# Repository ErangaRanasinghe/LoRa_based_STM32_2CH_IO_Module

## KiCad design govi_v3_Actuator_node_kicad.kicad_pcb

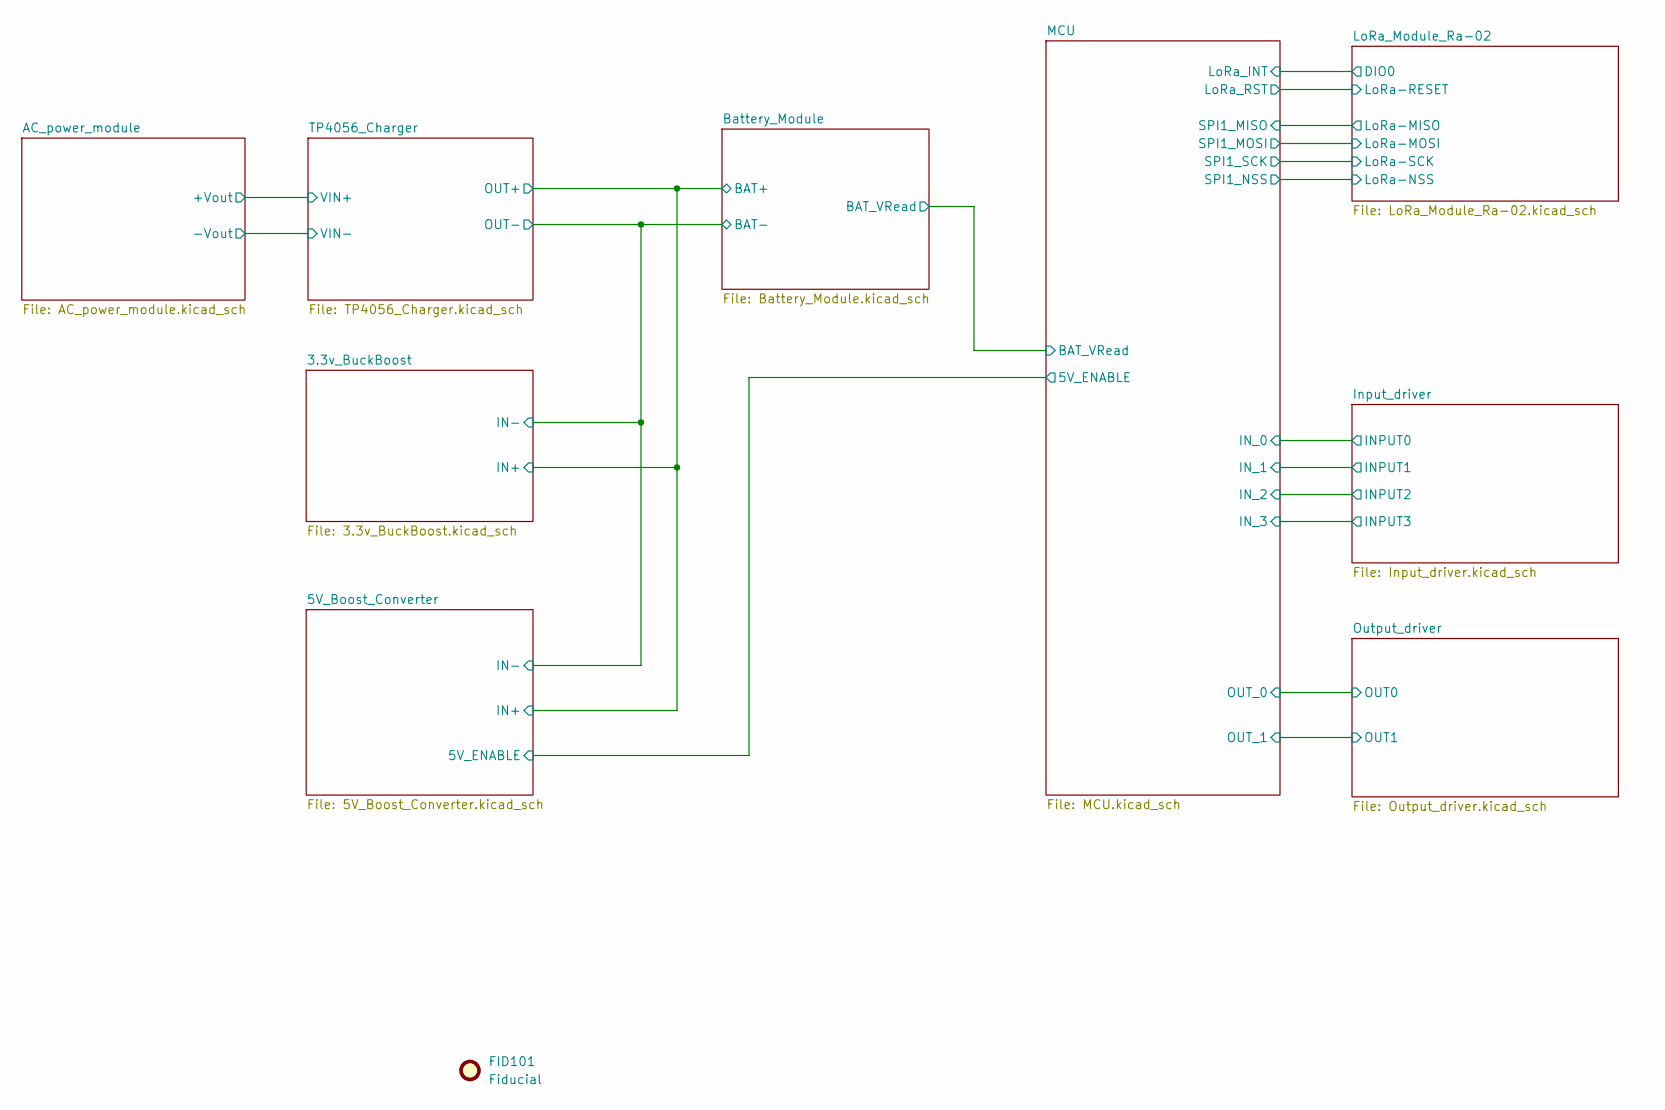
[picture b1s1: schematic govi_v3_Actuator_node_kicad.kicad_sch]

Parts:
FID101: Fiducial; Fiducial_1mm_Mask3mm

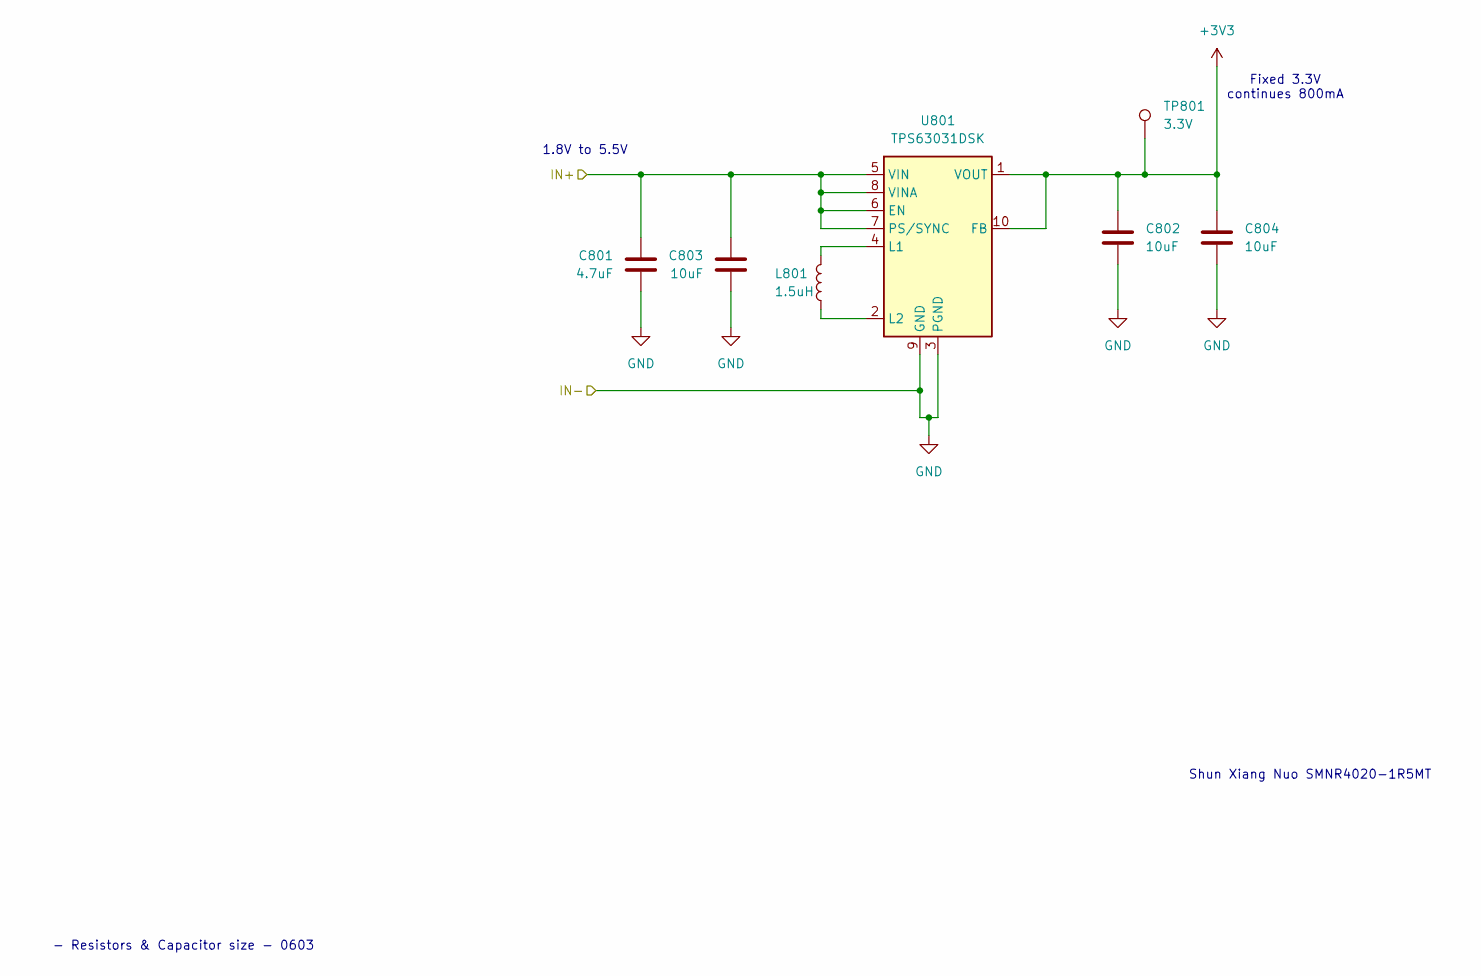
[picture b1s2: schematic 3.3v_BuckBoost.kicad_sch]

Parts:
C801: 4.7uF; C_0603_1608Metric_Pad1.08x0.95mm_HandSolder
C802, C803, C804: 10uF; C_0603_1608Metric_Pad1.08x0.95mm_HandSolder
L801: 1.5uH; L_KOHERelec_MDA7030
TP801: 3.3V; TestPoint_Pad_D1.0mm
U801: TPS63031DSK; WSON-10-1EP_2.5x2.5mm_P0.5mm_EP1.2x2mm

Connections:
+3V3: C802.1, C804.1, TP801.1, U801.1 (VOUT), U801.10 (FB); also elsewhere on the board
/Battery_Module/BAT(+): C801.1, C803.1, U801.5 (VIN), U801.6 (EN), U801.7 (PS/SYNC), U801.8 (VINA); also elsewhere on the board
GND: C801.2, C802.2, C803.2, C804.2, U801.3 (PGND), U801.9 (GND), U801.11 (PGND); also elsewhere on the board
unnamed: L801.1, U801.4 (L1)
unnamed: L801.2, U801.2 (L2)

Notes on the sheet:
Shun Xiang Nuo SMNR4020-1R5MT
- Resistors & Capacitor size - 0603
1.8V to 5.5V
Fixed 3.3V continues 800mA

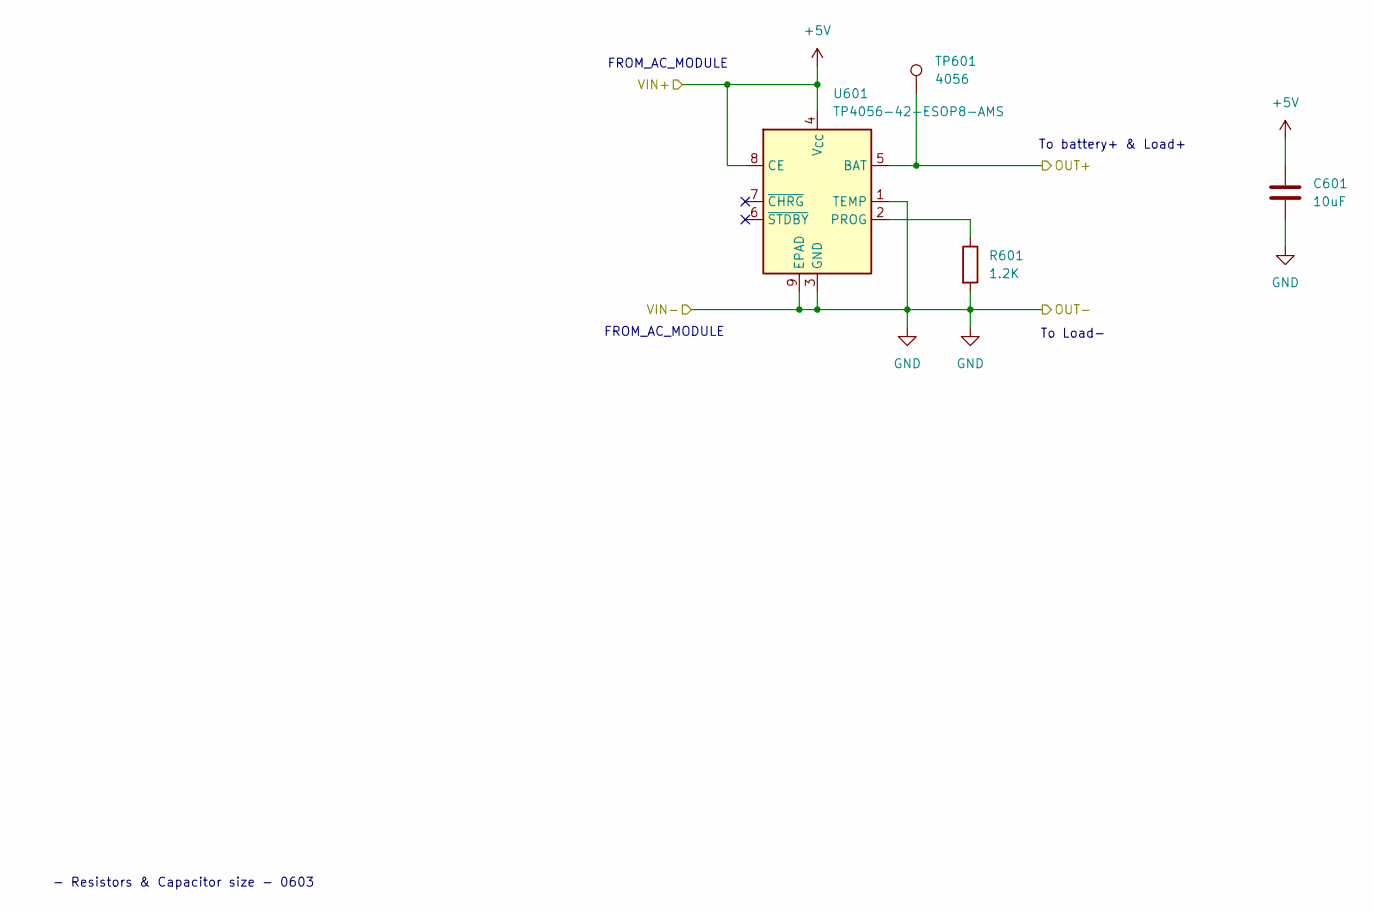
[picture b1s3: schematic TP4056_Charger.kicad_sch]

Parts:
C601: 10uF; C_0603_1608Metric_Pad1.08x0.95mm_HandSolder
R601: 1.2K; R_0603_1608Metric_Pad0.98x0.95mm_HandSolder
TP601: 4056; TestPoint_Pad_D1.0mm
U601: TP4056-42-ESOP8-AMS; SOIC-8-1EP_3.9x4.9mm_P1.27mm_EP2.41x3.3mm_ThermalVias

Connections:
+5V: C601.1, U601.4 (V_{CC}), U601.8 (CE); also elsewhere on the board
/Battery_Module/BAT(+): TP601.1, U601.5 (BAT); also elsewhere on the board
GND: C601.2, R601.2, U601.1 (TEMP), U601.3 (GND), U601.9 (EPAD); also elsewhere on the board
unnamed: R601.1, U601.2 (PROG)

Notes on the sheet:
- Resistors & Capacitor size - 0603
To battery+ & Load+
To Load-
FROM_AC_MODULE

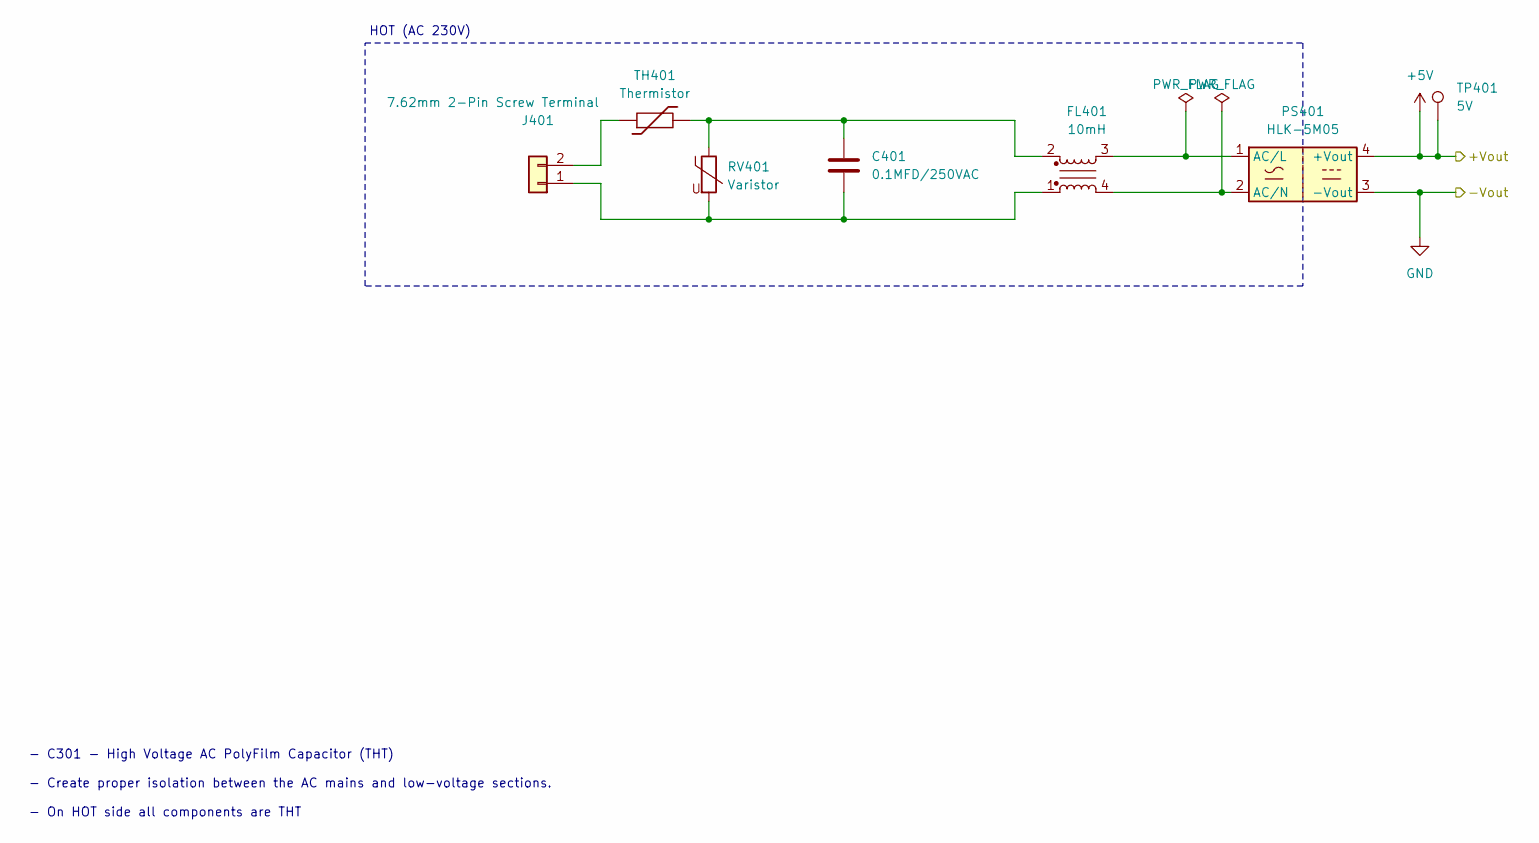
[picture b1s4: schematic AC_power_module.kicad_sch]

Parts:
C401: 0.1MFD/250VAC; C_Rect_L11.5mm_W5.0mm_P10.00mm_MKT
FL401: 10mH; B82730U3451A020-ferrite-core-inductor
J401: 7.62mm 2-Pin Screw Terminal; PhoenixContact_MCV_1,5_2-G-5.08_1x02_P5.08mm_Vertical
PS401: HLK-5M05; HLK5M05
RV401: Varistor; RV_Disc_D12mm_W5.1mm_P7.5mm
TH401: Thermistor; B57236S0250M000-Thermister
TP401: 5V; TestPoint_Pad_D1.0mm

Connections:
+5V: PS401.4 (+Vout), TP401.1; also elsewhere on the board
GND: PS401.3 (-Vout); also elsewhere on the board
unnamed: C401.1, FL401.2, RV401.1, TH401.2
unnamed: C401.2, FL401.1, J401.1, RV401.2
unnamed: J401.2, TH401.1
unnamed: FL401.3, PS401.1 (AC/L)
unnamed: FL401.4, PS401.2 (AC/N)

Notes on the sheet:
HOT (AC 230V)
- C301 - High Voltage AC PolyFilm Capacitor (THT) - Create proper isolation between the AC mains and low-voltage sections. - On HOT side all components are THT

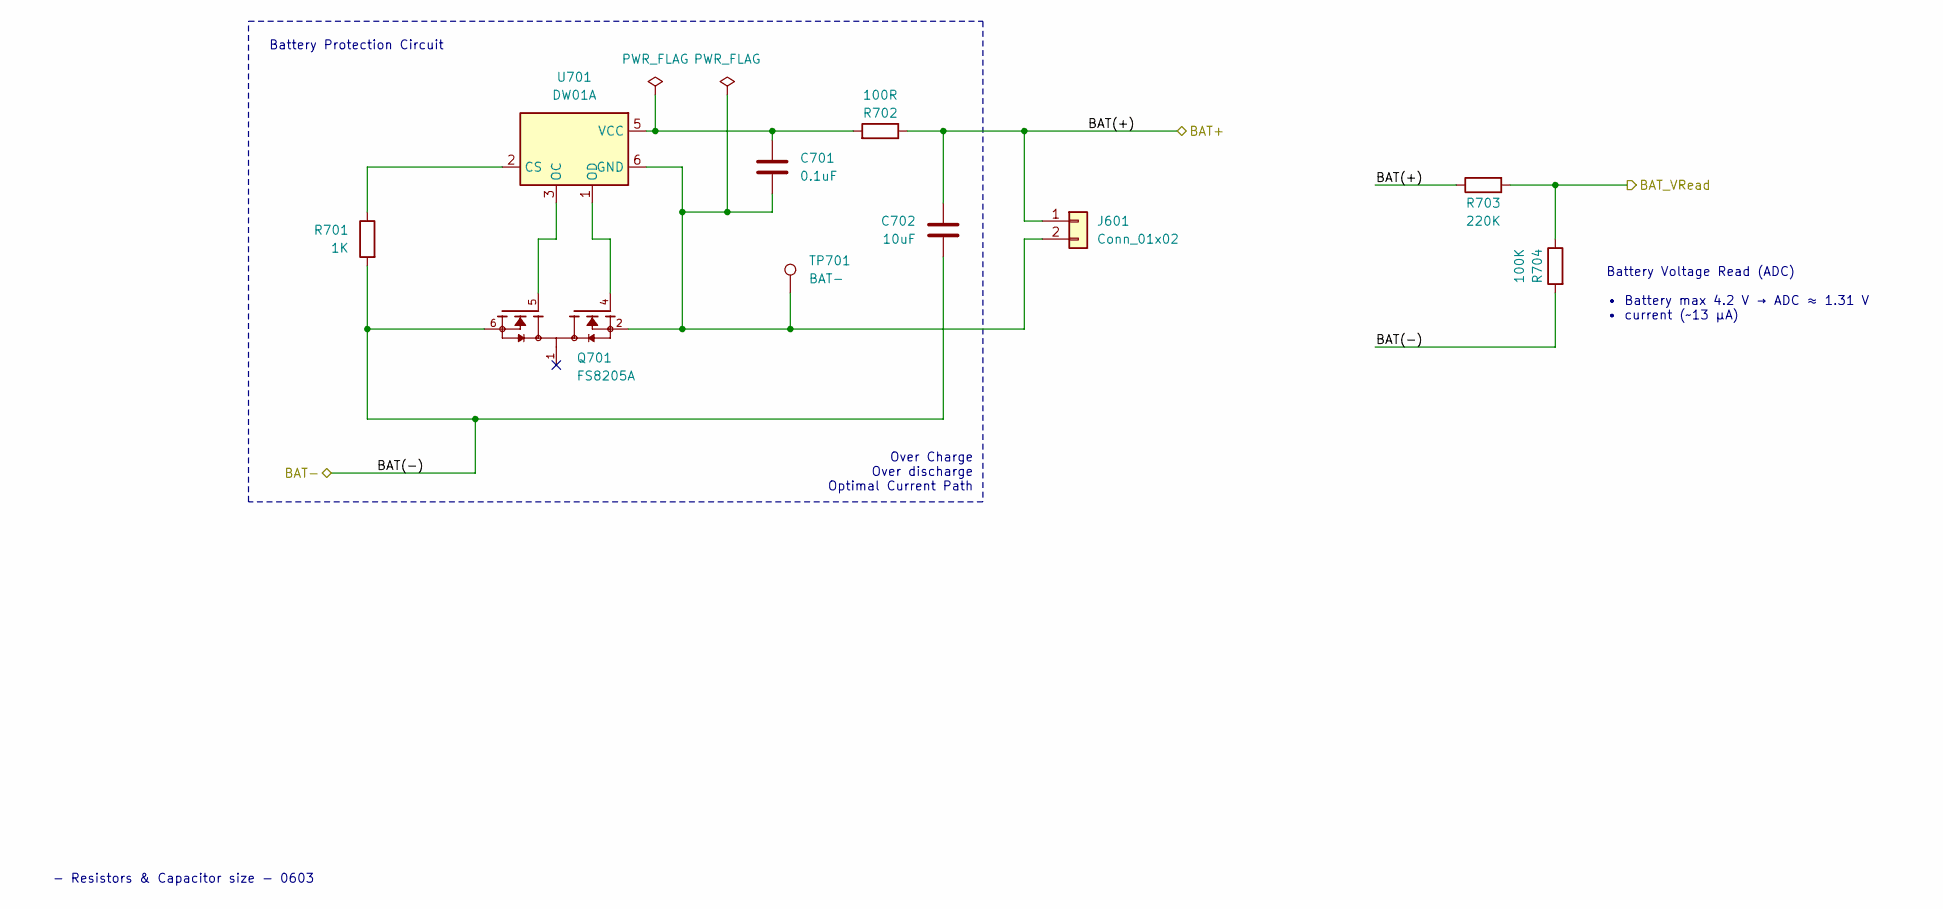
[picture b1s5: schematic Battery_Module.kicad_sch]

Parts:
C701: 0.1uF; C_0603_1608Metric_Pad1.08x0.95mm_HandSolder
C702: 10uF; C_0603_1608Metric_Pad1.08x0.95mm_HandSolder
J601: Conn_01x02; PhoenixContact_MCV_1,5_2-G-5.08_1x02_P5.08mm_Vertical
Q701: FS8205A; SOP65P640X120-8N; PARTREV 1.7
R701: 1K; R_0603_1608Metric_Pad0.98x0.95mm_HandSolder
R702: 100R; R_0603_1608Metric_Pad0.98x0.95mm_HandSolder
R703: 220K; R_0603_1608Metric_Pad0.98x0.95mm_HandSolder
R704: 100K; R_0603_1608Metric_Pad0.98x0.95mm_HandSolder
TP701: BAT-; TestPoint_Pad_D1.0mm
U701: DW01A; SOT-23-6

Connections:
/Battery_Module/BAT(+): C702.1, J601.1, R702.1, R703.1; also elsewhere on the board
/Battery_Module/BAT_VRead: R703.2, R704.1; also elsewhere on the board
GND: C702.2, Q701.6, Q701.7, R701.2, R704.2; also elsewhere on the board
unnamed: C701.2, J601.2, Q701.2, Q701.3, TP701.1, U701.6 (GND)
unnamed: R701.1, U701.2 (CS)
unnamed: Q701.5, U701.3 (OC)
unnamed: Q701.4, U701.1 (OD)
unnamed: C701.1, R702.2, U701.5 (VCC)

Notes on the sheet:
Over Charge Over discharge Optimal Current Path
- Resistors & Capacitor size - 0603
Battery Protection Circuit
Battery Voltage Read (ADC) • Battery max 4.2 V → ADC ≈ 1.31 V • current (~13 µA)

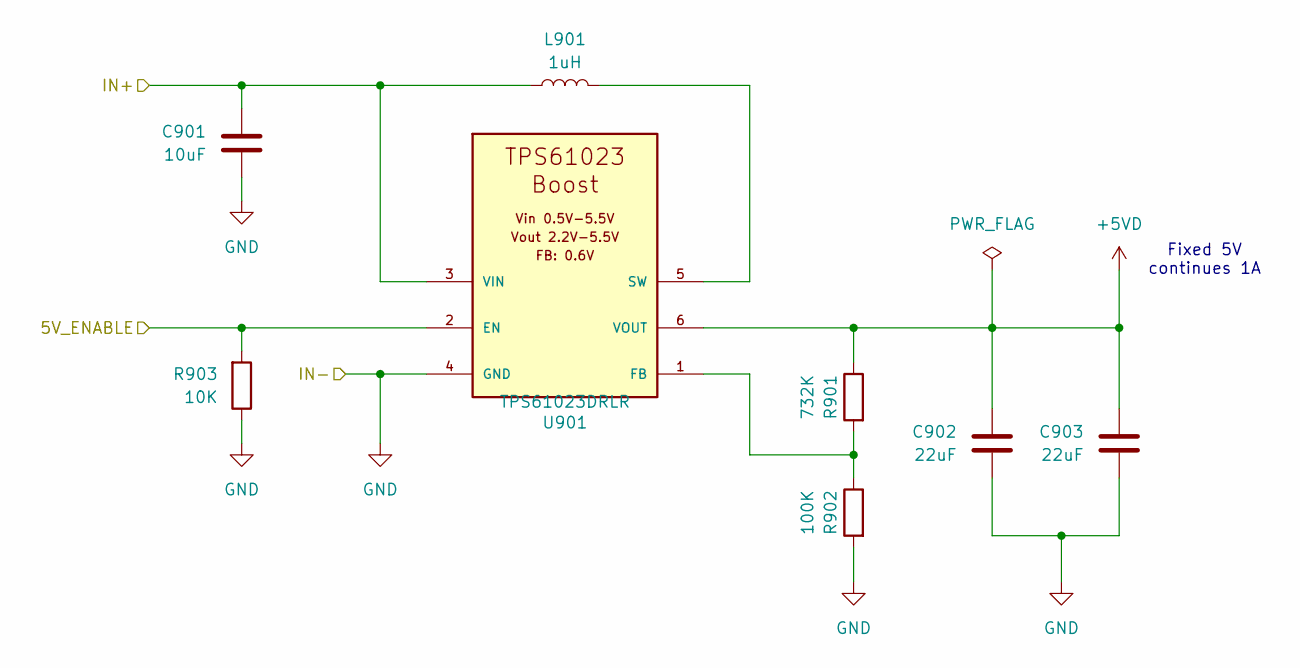
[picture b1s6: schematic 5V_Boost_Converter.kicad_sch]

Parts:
C901: 10uF; C_0603_1608Metric_Pad1.08x0.95mm_HandSolder
C902, C903: 22uF; C_0603_1608Metric_Pad1.08x0.95mm_HandSolder
L901: 1uH; L_Cenker_CKCS4030
R901: 732K; R_0603_1608Metric_Pad0.98x0.95mm_HandSolder
R902: 100K; R_0603_1608Metric_Pad0.98x0.95mm_HandSolder
R903: 10K; R_0402_1005Metric_Pad0.72x0.64mm_HandSolder
U901: TPS61023DRLR; SOT563-ORI

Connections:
+5VD: C902.1, C903.1, R901.1, U901.6 (VOUT); also elsewhere on the board
/5V_Boost_Converter/5V_ENABLE: R903.2, U901.2 (EN); also elsewhere on the board
/Battery_Module/BAT(+): C901.1, L901.1, U901.3 (VIN); also elsewhere on the board
GND: C901.2, C902.2, C903.2, R902.2, R903.1, U901.4 (GND); also elsewhere on the board
unnamed: R901.2, R902.1, U901.1 (FB)
unnamed: L901.2, U901.5 (SW)

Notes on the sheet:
Fixed 5V continues 1A

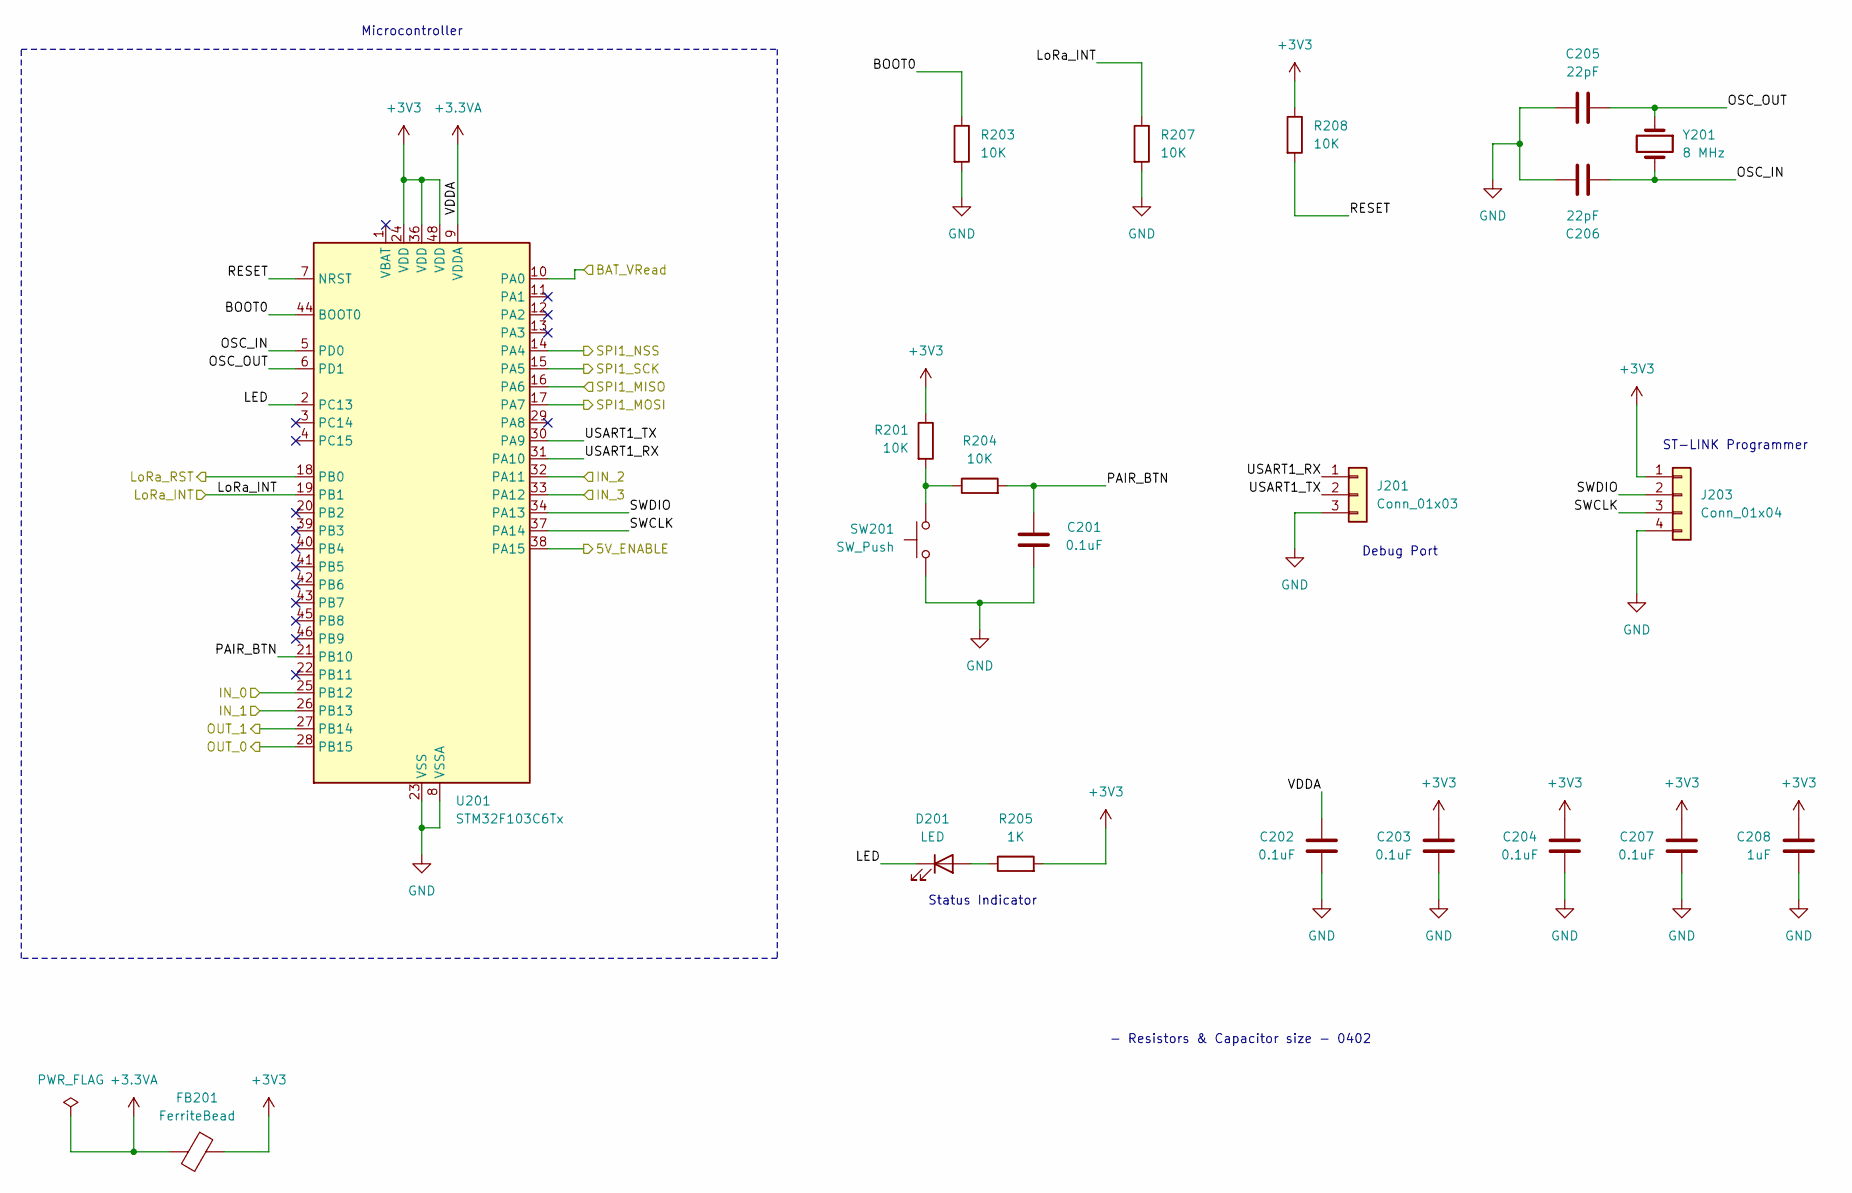
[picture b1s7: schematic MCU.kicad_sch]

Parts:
C201, C202, C203, C204, C207: 0.1uF; C_0402_1005Metric_Pad0.74x0.62mm_HandSolder
C205, C206: 22pF; C_0402_1005Metric_Pad0.74x0.62mm_HandSolder
C208: 1uF; C_0402_1005Metric_Pad0.74x0.62mm_HandSolder
D201: LED; LED_D3.0mm
FB201: FerriteBead; R_0402_1005Metric_Pad0.72x0.64mm_HandSolder
J201: Conn_01x03; PinHeader_1x03_P2.54mm_Vertical
J203: Conn_01x04; PinHeader_1x04_P2.54mm_Vertical
R201, R203, R204, R207, R208: 10K; R_0402_1005Metric_Pad0.72x0.64mm_HandSolder
R205: 1K; R_0402_1005Metric_Pad0.72x0.64mm_HandSolder
SW201: SW_Push; PinHeader_1x02_P2.54mm_Vertical
U201: STM32F103C6Tx; LQFP-48_7x7mm_P0.5mm
Y201: 8 MHz; Crystal_HC49-4H_Vertical

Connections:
+3.3VA: C202.1, FB201.2, U201.9 (VDDA)
+3V3: C203.1, C204.1, C207.1, C208.1, FB201.1, J203.1, R201.1, R205.2, R208.1, U201.24 (VDD), U201.36 (VDD), U201.48 (VDD); also elsewhere on the board
/5V_Boost_Converter/5V_ENABLE: U201.38 (PA15); also elsewhere on the board
/Battery_Module/BAT_VRead: U201.10 (PA0); also elsewhere on the board
/Input_driver/INPUT0: U201.25 (PB12); also elsewhere on the board
/Input_driver/INPUT1: U201.26 (PB13); also elsewhere on the board
/Input_driver/INPUT2: U201.32 (PA11); also elsewhere on the board
/Input_driver/INPUT3: U201.33 (PA12); also elsewhere on the board
/LoRa_Module_Ra-02/LoRa-MISO: U201.16 (PA6); also elsewhere on the board
/LoRa_Module_Ra-02/LoRa-MOSI: U201.17 (PA7); also elsewhere on the board
/LoRa_Module_Ra-02/LoRa-NSS: U201.14 (PA4); also elsewhere on the board
/LoRa_Module_Ra-02/LoRa-RESET: U201.18 (PB0); also elsewhere on the board
/LoRa_Module_Ra-02/LoRa-SCK: U201.15 (PA5); also elsewhere on the board
/MCU/BOOT0: R203.1, U201.44 (BOOT0)
/MCU/LED: D201.1 (K), U201.2 (PC13)
/MCU/LoRa_INT: R207.1, U201.19 (PB1); also elsewhere on the board
/MCU/OSC_IN: C206.1, U201.5 (PD0), Y201.2
/MCU/OSC_OUT: C205.1, U201.6 (PD1), Y201.1
/MCU/OUT_0: U201.28 (PB15); also elsewhere on the board
/MCU/OUT_1: U201.27 (PB14); also elsewhere on the board
/MCU/PAIR_BTN: C201.1, R204.2, U201.21 (PB10)
/MCU/RESET: R208.2, U201.7 (NRST)
/MCU/SWCLK: J203.3, U201.37 (PA14)
/MCU/SWDIO: J203.2, U201.34 (PA13)
/MCU/USART1_RX: J201.1, U201.31 (PA10)
/MCU/USART1_TX: J201.2, U201.30 (PA9)
GND: C201.2, C202.2, C203.2, C204.2, C205.2, C206.2, C207.2, C208.2, J201.3, J203.4, R203.2, R207.2, SW201.1, U201.8 (VSSA), U201.23 (VSS), U201.35 (VSS), U201.47 (VSS); also elsewhere on the board
unnamed: D201.2 (A), R205.1
unnamed: R201.2, R204.1, SW201.2

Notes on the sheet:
Status Indicator
Debug Port
- Resistors & Capacitor size - 0402
ST-LINK Programmer
Microcontroller

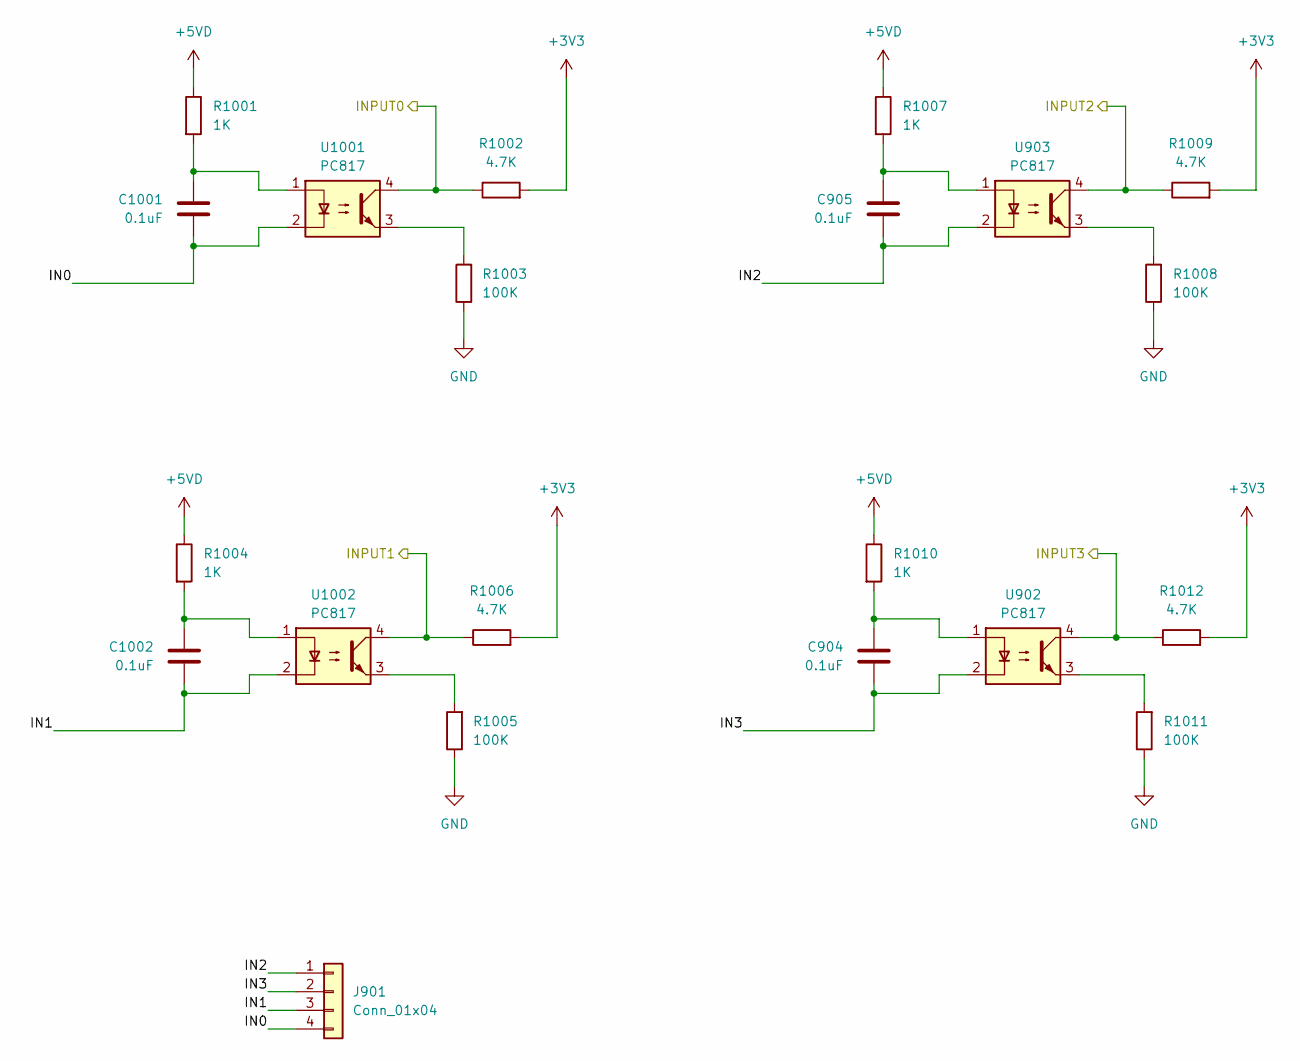
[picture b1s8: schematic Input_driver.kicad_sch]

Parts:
C904, C905, C1001, C1002: 0.1uF; C_0402_1005Metric_Pad0.74x0.62mm_HandSolder
J901: Conn_01x04; PhoenixContact_MCV_1,5_4-G-5.08_1x04_P5.08mm_Vertical
R1001, R1004, R1007, R1010: 1K; R_0603_1608Metric_Pad0.98x0.95mm_HandSolder
R1002, R1006, R1009, R1012: 4.7K; R_0402_1005Metric_Pad0.72x0.64mm_HandSolder
R1003, R1005, R1008, R1011: 100K; R_0402_1005Metric_Pad0.72x0.64mm_HandSolder
U902, U903, U1001, U1002: PC817; DIP-4_W7.62mm

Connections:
+3V3: R1002.2, R1006.2, R1009.2, R1012.2; also elsewhere on the board
+5VD: R1001.1, R1004.1, R1007.1, R1010.1; also elsewhere on the board
/Input_driver/IN0: C1001.2, J901.4, U1001.2
/Input_driver/IN1: C1002.2, J901.3, U1002.2
/Input_driver/IN2: C905.2, J901.1, U903.2
/Input_driver/IN3: C904.2, J901.2, U902.2
/Input_driver/INPUT0: R1002.1, U1001.4; also elsewhere on the board
/Input_driver/INPUT1: R1006.1, U1002.4; also elsewhere on the board
/Input_driver/INPUT2: R1009.1, U903.4; also elsewhere on the board
/Input_driver/INPUT3: R1012.1, U902.4; also elsewhere on the board
GND: R1003.1, R1005.1, R1008.1, R1011.1; also elsewhere on the board
unnamed: C904.1, R1010.2, U902.1
unnamed: C905.1, R1007.2, U903.1
unnamed: C1001.1, R1001.2, U1001.1
unnamed: C1002.1, R1004.2, U1002.1
unnamed: R1003.2, U1001.3
unnamed: R1005.2, U1002.3
unnamed: R1008.2, U903.3
unnamed: R1011.2, U902.3

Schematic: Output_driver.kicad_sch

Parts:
C1101, C1102: 0.1uF; C_0402_1005Metric_Pad0.74x0.62mm_HandSolder
J1001: Conn_01x04; PhoenixContact_MCV_1,5_4-G-5.08_1x04_P5.08mm_Vertical
Q1002, Q1101: BC817-40; SOT-23
R1101, R1104: 10R 0805; R_0805_2012Metric_Pad1.20x1.40mm_HandSolder
R1102, R1103: 1K; R_0603_1608Metric_Pad0.98x0.95mm_HandSolder
U1101, U1102: G3MB-202P; G3MB202PLDC5

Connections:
+5VD: R1101.1, R1104.1; also elsewhere on the board
/MCU/OUT_0: R1102.1; also elsewhere on the board
/MCU/OUT_1: R1103.1; also elsewhere on the board
/Output_driver/OUT0_11: J1001.2, U1101.11
/Output_driver/OUT0_14: J1001.1, U1101.14
/Output_driver/OUT1_11: J1001.4, U1102.11
/Output_driver/OUT1_14: J1001.3, U1102.14
GND: Q1002.2 (E), Q1101.2 (E); also elsewhere on the board
unnamed: C1101.1, R1101.2, U1101.A1
unnamed: C1102.1, R1104.2, U1102.A1
unnamed: Q1002.1 (B), R1103.2
unnamed: C1102.2, Q1002.3 (C), U1102.A2
unnamed: Q1101.1 (B), R1102.2
unnamed: C1101.2, Q1101.3 (C), U1101.A2

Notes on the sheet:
BC817-40,215 Nxperia

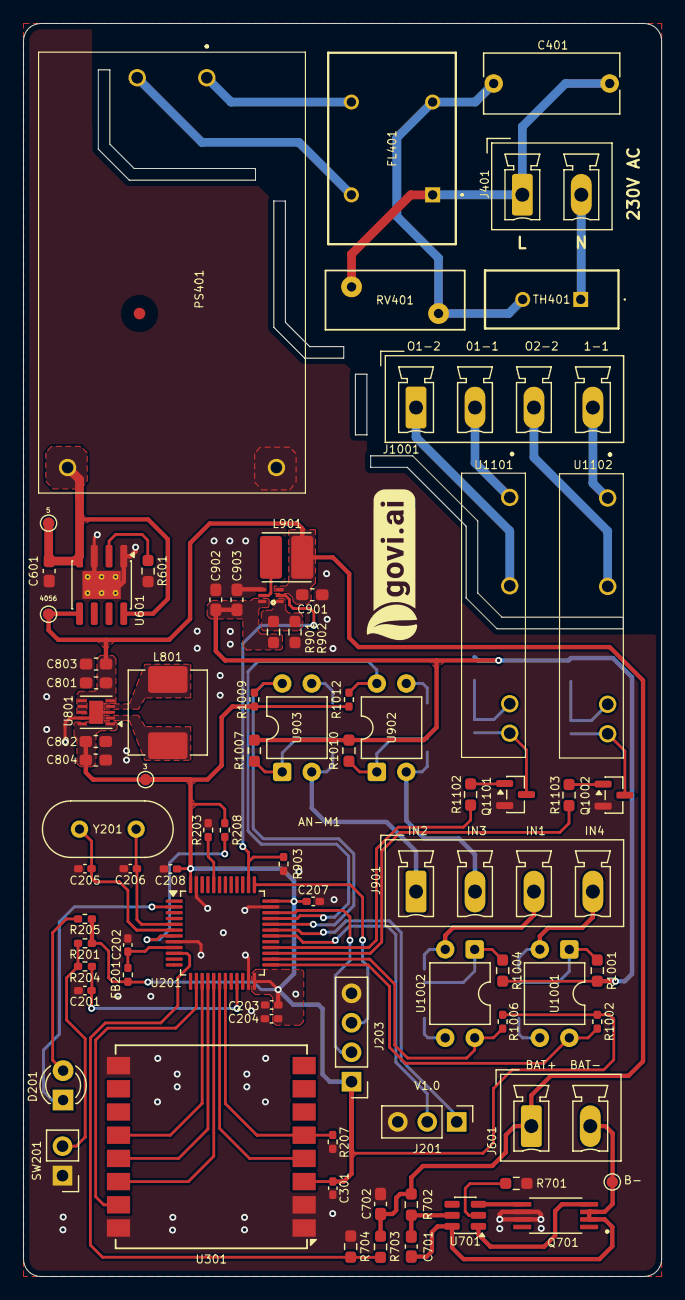
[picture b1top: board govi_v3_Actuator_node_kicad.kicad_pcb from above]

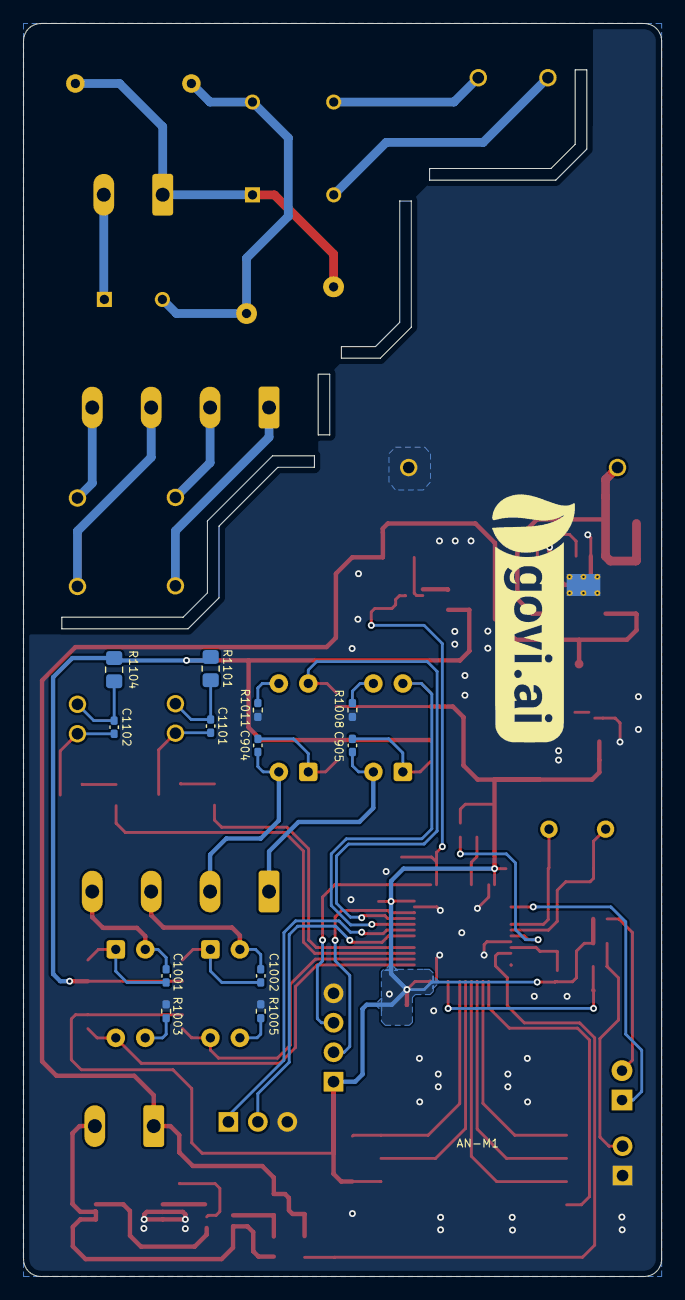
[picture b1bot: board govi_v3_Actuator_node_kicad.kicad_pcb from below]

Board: 2 copper layers, 55.0 x 108.0 mm, 92 parts (12 on the bottom side), 69 nets.

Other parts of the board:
C301: 0.1uF; C_0402_1005Metric_Pad0.74x0.62mm_HandSolder
U301: Ra-02; Ai-Thinker-Ra-01-LoRa

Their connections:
+3V3: C301.1, U301.3 (VDD); also elsewhere on the board
/LoRa_Module_Ra-02/LoRa-MISO: U301.13 (MISO); also elsewhere on the board
/LoRa_Module_Ra-02/LoRa-MOSI: U301.14 (MOSI); also elsewhere on the board
/LoRa_Module_Ra-02/LoRa-NSS: U301.15 (~NSS); also elsewhere on the board
/LoRa_Module_Ra-02/LoRa-RESET: U301.4 (~RESET); also elsewhere on the board
/LoRa_Module_Ra-02/LoRa-SCK: U301.12 (SCK); also elsewhere on the board
/MCU/LoRa_INT: U301.5 (DIO0); also elsewhere on the board
GND: C301.2, U301.1 (GND), U301.2 (GND), U301.9 (GND), U301.16 (GND); also elsewhere on the board

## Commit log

2026-01-02 "initial commit"
2026-01-08 "V1.0 final design"
